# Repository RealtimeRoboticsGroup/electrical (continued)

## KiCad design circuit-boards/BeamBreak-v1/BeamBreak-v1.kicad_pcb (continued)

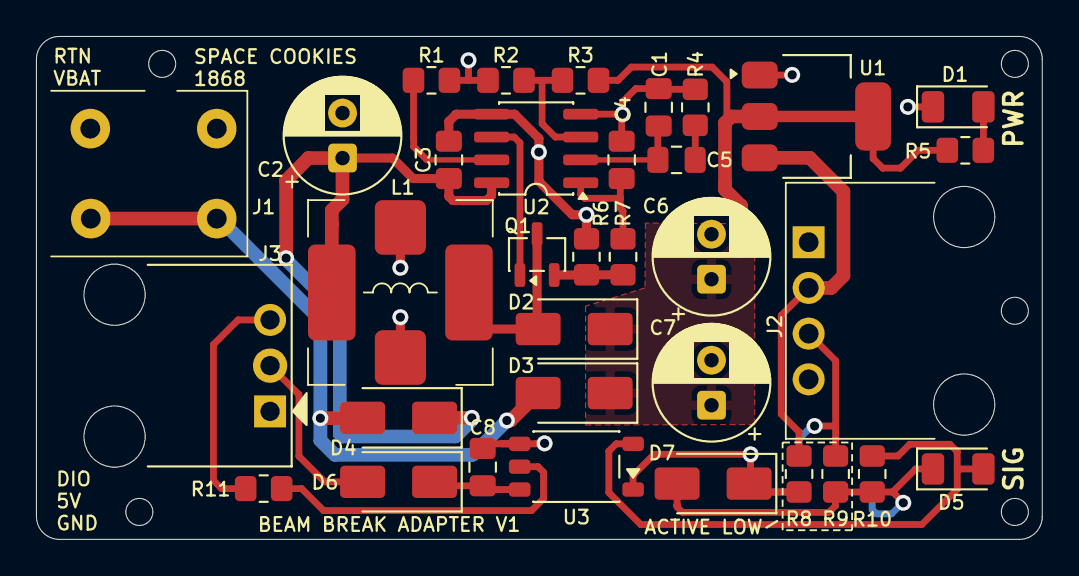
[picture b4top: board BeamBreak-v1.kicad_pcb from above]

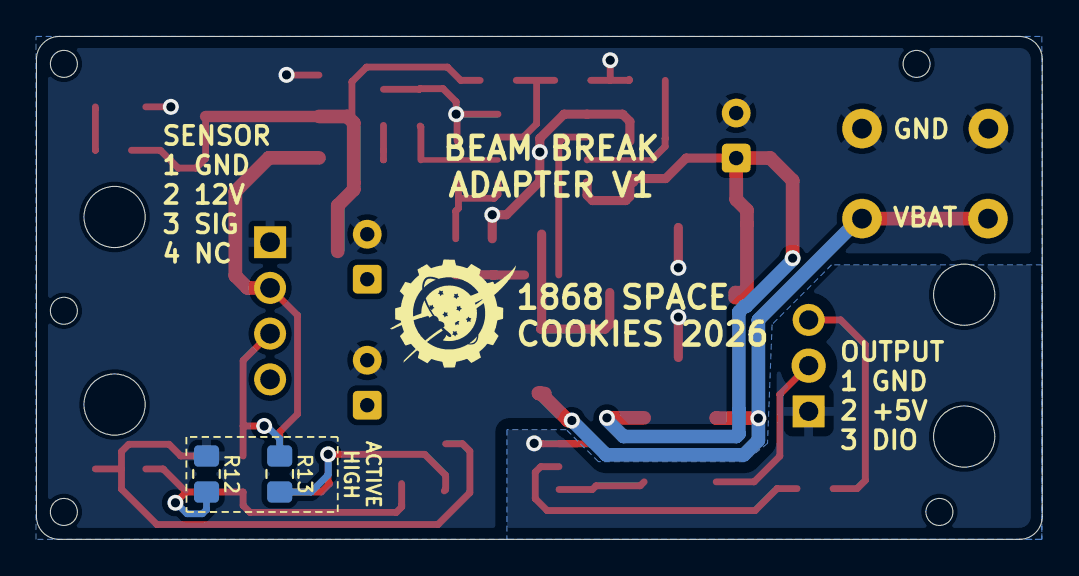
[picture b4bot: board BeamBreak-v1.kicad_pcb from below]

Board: 2 copper layers, 55.9 x 27.9 mm, 41 parts (3 on the bottom side), 23 nets.

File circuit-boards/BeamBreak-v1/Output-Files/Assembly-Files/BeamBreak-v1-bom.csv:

"Item","QUANTITY","Reference","Value","MFG","MFG P/N","DIST","DIST P/N"
"1","1","C1","1nF-50V-5%-0805","KEMET","C0805C102J5GACTU","Digikey","399-C0805C102J5GACTUCT-ND"
"2","1","C4","10pF-50V-5%-0805","YAGEO","CC0805JRNPO9BN100","Digikey","311-1099-1-ND"
"3","1","C5","22nF-50V-5%-0805","TDK Corporation","C2012C0G1H223J125AA","Digikey","445-7522-1-ND"
"4","3","C2,C6,C7","100uF-20%-35V","KYOCERA AVX","RPF0608101M035K","Digikey","478-RPF0608101M035KCT-ND"
"5","2","C3,C8","0.1uF-50V-5%-0805","KEMET","C0805C104J5RACTU","Digikey","399-C0805C104J5RACTUCT-ND"
"6","1","D1","PWR","Everlight","QTLP650D4TR/QT15-21SYGD/S530-E2/TR8","Digikey","1080-1419-1-ND"
"7","1","D5","SIG","Everlight","QTLP650D3TR","Digikey","1080-1418-1-ND"
"8","5","D2-D4,D6,D7","B340AE-13","Diodes Inc","B340AE-13","Digikey","B340AE-13DICT-ND"
"9","1","J1","Power","Weidmuller","1824740000","Digikey","281-2110-ND"
"10","1","J2","SENSOR","Molex","70555-0038","Digikey","WM4177-ND"
"11","1","J3","OUT","Molex","70555-0037","Digikey","WM4176-ND"
"12","1","L1","33uH-159m-20%","Vishay Dale","IHLE5050FHER6R8M5A","Digikey","541-IHLE5050FHER6R8M5ACT-ND"
"13","1","Q1","SI2318CDS-T1-GE3","Vishay Siliconix","SI2318CDS-T1-GE3","Digikey","SI2318CDS-T1-GE3CT-ND"
"14","1","R1","59.0k-1%-0805","YAGEO","RC0805FR-0759KL","Digikey","311-59.0KCRCT-ND"
"15","1","R2","1k-1%-0805","YAGEO","RC0805FR-071KL","Digikey","311-1.00KCRCT-ND"
"16","1","R3","8.66k-1%-0805","Stackpole Electronics Inc","RMCF0805FT8K66","Digikey","RMCF0805FT8K66CT-ND"
"17","1","R4","7.32k-1%-0805","Panasonic Electronic Components","ERJ-6ENF7321V","Digikey","P7.32KCCT-ND"
"18","1","R5","2k-1%-0805","Vishay Dale","CRCW08052K00FKEA","Digikey","541-2.00KCCT-ND"
"19","1","R6","50mOhm-1%-0805","Panasonic Electronic Components","ERJ-6BWFR050V","Digikey","P17581CT-ND"
"20","2","R7,R11","100R-1%-0805","TE Connectivity Passive Product","CRG0805F100R","Digikey","A106053CT-ND"
"21","3","R8-R10","499R-1%-0805","YAGEO","RC0805FR-07499RL","Digikey","311-499CRCT-ND"
"22","1","U1","ITS41k0S-ME-N","Infineon","ITS41K0SMENHUMA1","Digikey","ITS41K0SMENHUMA1CT-ND"
"23","1","U2","LM3478MA","Texas Instruments","LM3478MAX/NOPB","Digikey","296-38111-1-ND"
"24","1","U3","TLP2361(TPL,E","Toshiba Semiconductor and Storage","TLP2361(TPL,E","Digikey","TLP2361(TPLECT-ND"

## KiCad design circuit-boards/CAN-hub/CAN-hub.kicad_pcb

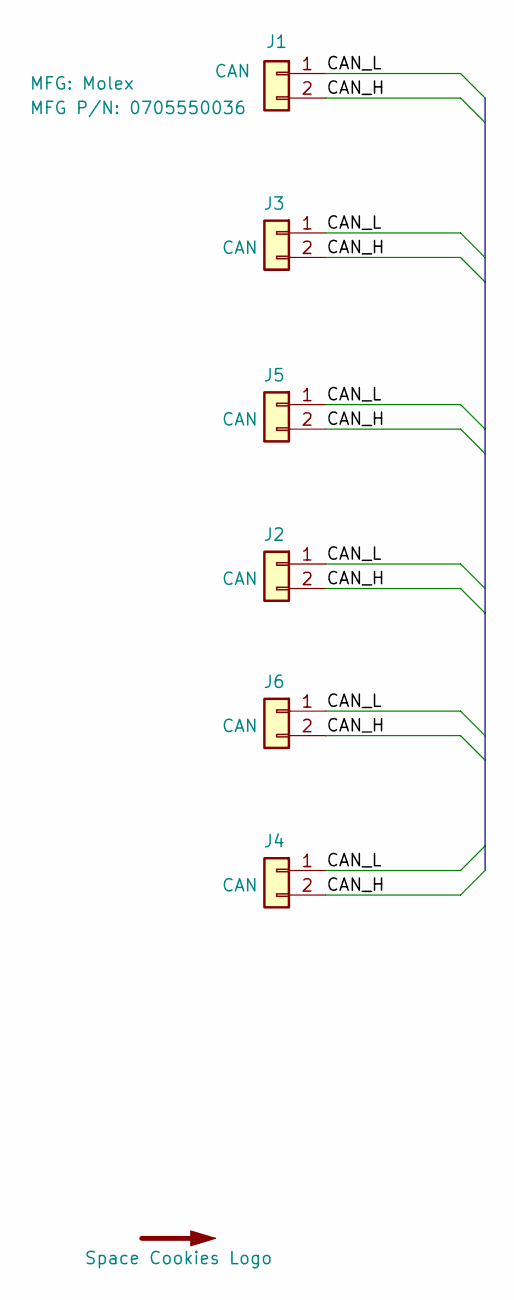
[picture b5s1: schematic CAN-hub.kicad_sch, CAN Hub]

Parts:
G1: Space Cookies Logo; SPACE_COOKIES_LOGO_7mm
J1, J2, J3, J4, J5, J6: CAN; Molex-70555-0001; MFG P/N 0705550036

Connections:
/CAN_H: J1.2, J2.2, J3.2, J4.2, J5.2, J6.2
/CAN_L: J1.1, J2.1, J3.1, J4.1, J5.1, J6.1

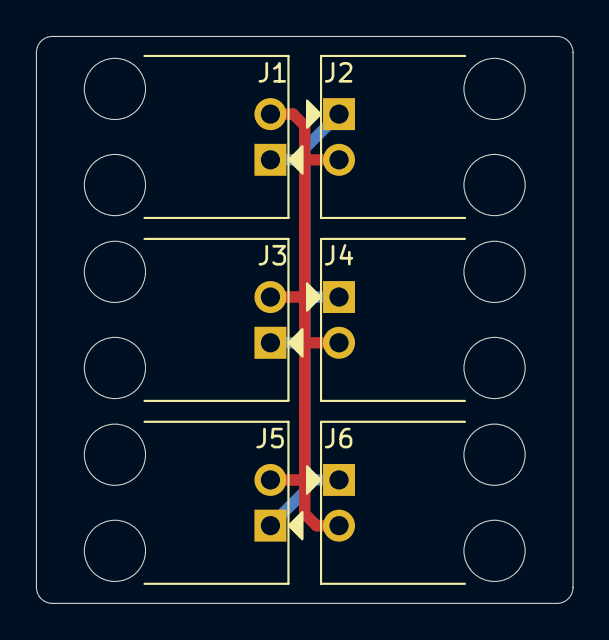
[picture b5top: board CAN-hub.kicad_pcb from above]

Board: 2 copper layers, 29.8 x 31.5 mm, 7 parts (1 on the bottom side), 2 nets.

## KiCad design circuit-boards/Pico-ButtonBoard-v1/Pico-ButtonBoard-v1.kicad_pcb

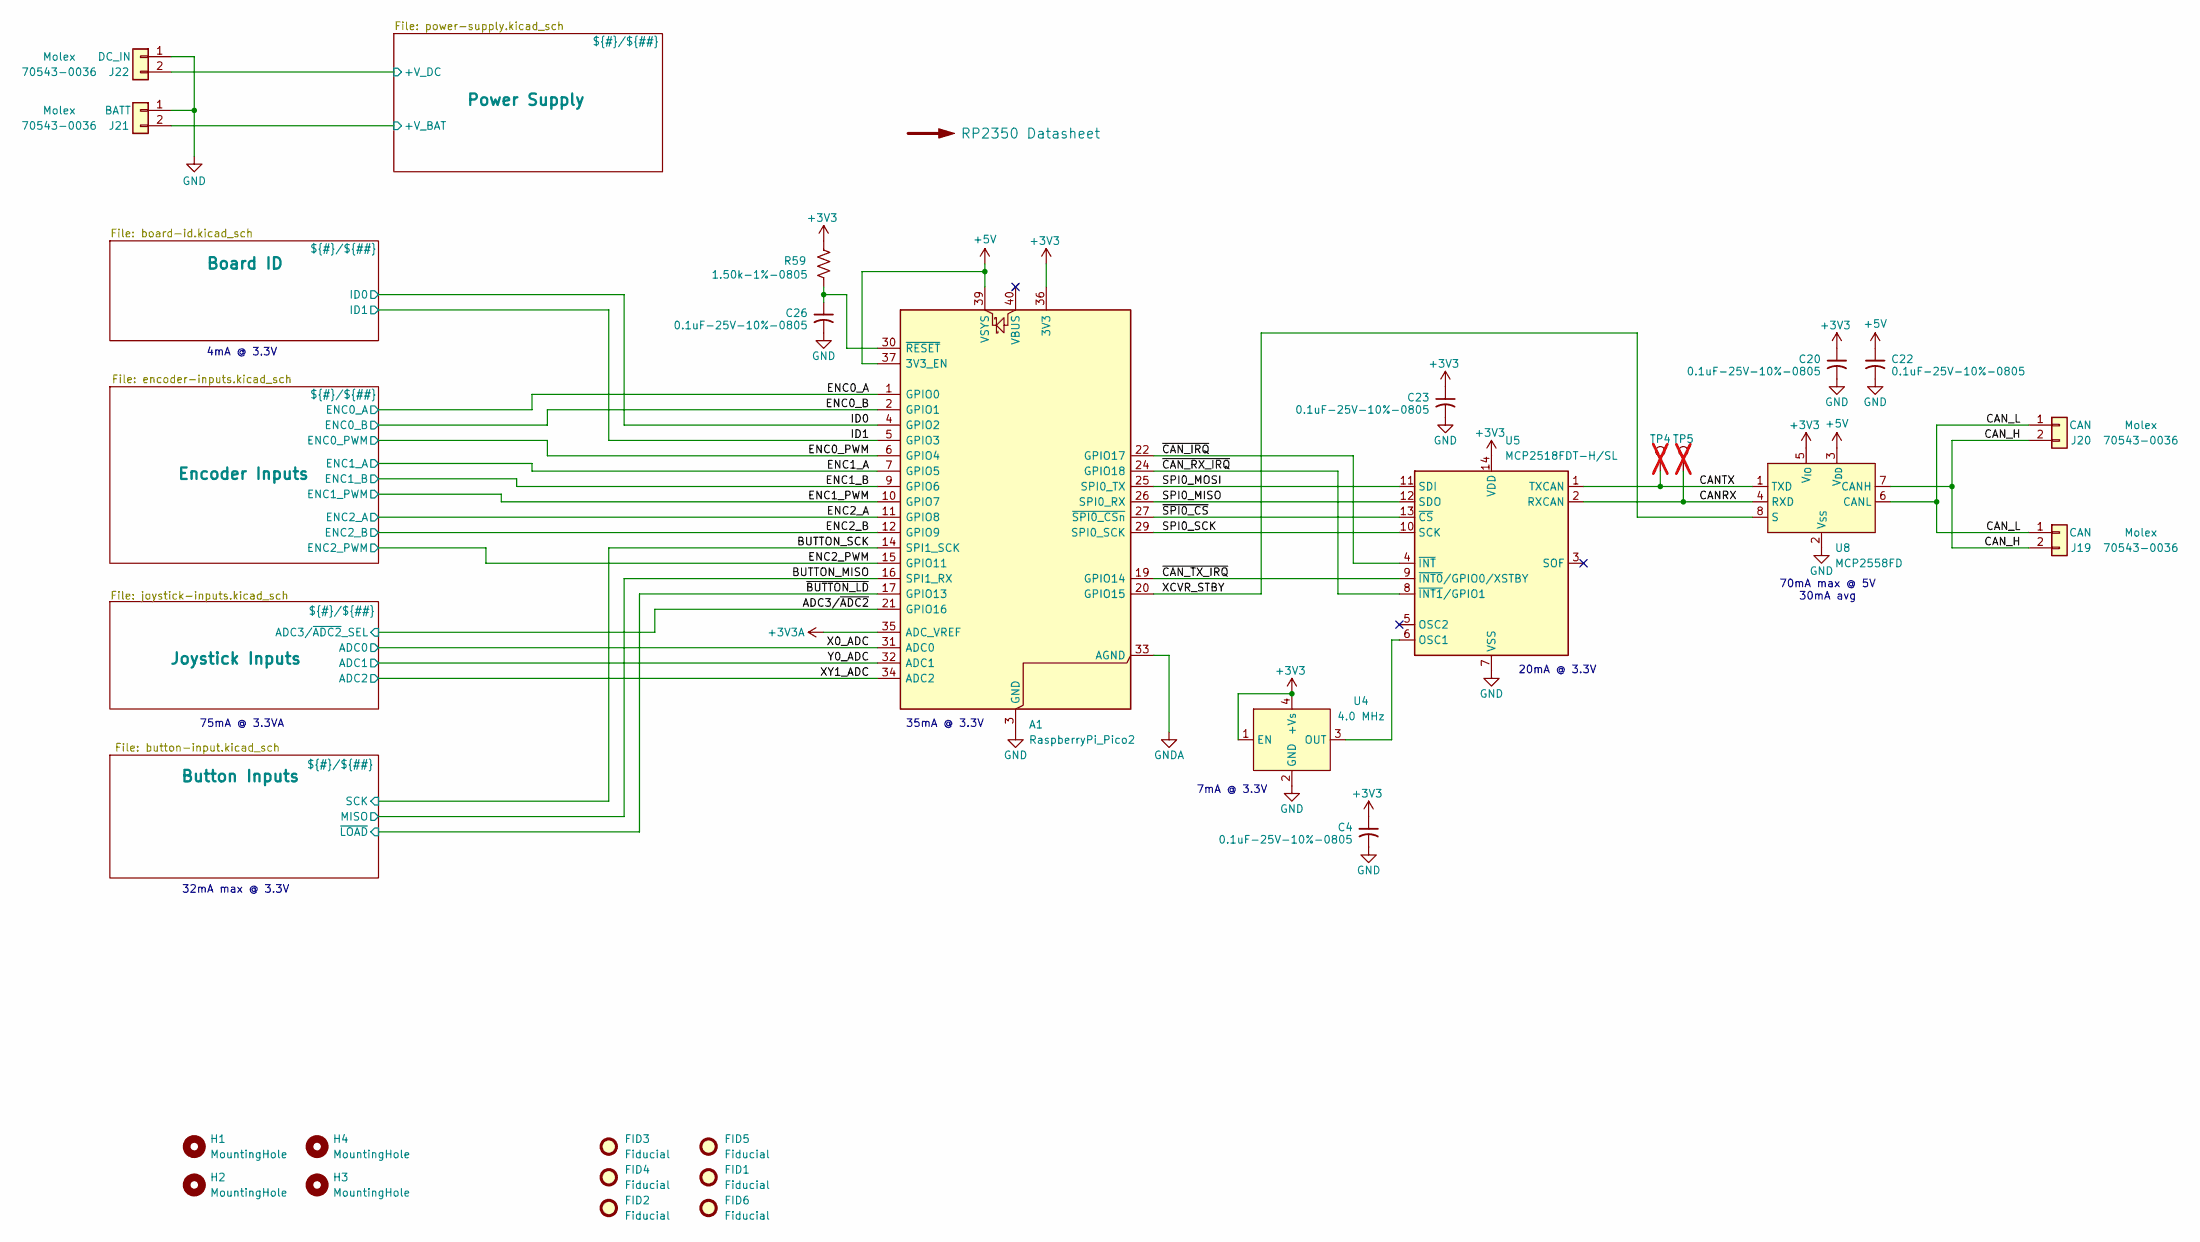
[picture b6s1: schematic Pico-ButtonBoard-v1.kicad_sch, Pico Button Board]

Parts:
A1: RaspberryPi_Pico2; RaspberryPi_Pico_Common_Unspecified
C4, C20, C22, C23, C26: 0.1uF-25V-10%-0805; C_0805_2012Metric_Pad1.18x1.45mm_HandSolder; MFG P/N 311-1141-1-ND
FID1, FID2, FID3, FID4, FID5, FID6: Fiducial; Fiducial_1.6mm_Mask3mm
H1, H2, H3, H4: MountingHole; MountingHole_3.2mm_M3
J19, J20: CAN; Molex-70543-0001; MFG P/N 70543-0036
J21: BATT; Molex-70543-0001; MFG P/N 70543-0036
J22: DC_IN; Molex-70543-0001; MFG P/N 70543-0036
R59: 1.50k-1%-0805; R_0805_2012Metric_Pad1.20x1.40mm_HandSolder; MFG P/N RC0805FR-071K5L
TP4: CAN_TX; TestPoint_Keystone_5000-5004_Miniature; not fitted
TP5: CAN_RX; TestPoint_Keystone_5000-5004_Miniature; not fitted
U4: 4.0 MHz; Wurth-CFPS-73; MFG P/N 831018041
U5: MCP2518FDT-H/SL; SO-14_3.9x8.65mm_P1.27mm; MFG P/N MCP2518FDT-H/SL
U8: MCP2558FD; SO-8_3.9x4.9mm_P1.27mm; MFG P/N MCP2558FD-H/SN

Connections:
+3V3: A1.36 (3V3), C4.1, C20.1, C23.1, R59.1, U4.1 (EN), U4.4 (+Vs), U5.14 (VDD), U8.5 (V_{IO}); also elsewhere on the board
+3V3A: A1.35 (ADC_VREF); also elsewhere on the board
+5V: A1.37 (3V3_EN), A1.39 (VSYS), C22.1, U8.3 (V_{DD}); also elsewhere on the board
/ADC3/~ADC2: A1.21 (GPIO16); also elsewhere on the board
/BUTTON_MISO: A1.16 (SPI1_RX); also elsewhere on the board
/BUTTON_SCK: A1.14 (SPI1_SCK); also elsewhere on the board
/CANRX: TP5.1, U5.2 (RXCAN), U8.4 (RXD)
/CANTX: TP4.1, U5.1 (TXCAN), U8.1 (TXD)
/CAN_H: J19.2, J20.2, U8.7 (CANH)
/CAN_L: J19.1, J20.1, U8.6 (CANL)
/ENC0_A: A1.1 (GPIO0); also elsewhere on the board
/ENC0_B: A1.2 (GPIO1); also elsewhere on the board
/ENC0_PWM: A1.6 (GPIO4); also elsewhere on the board
/ENC1_A: A1.7 (GPIO5); also elsewhere on the board
/ENC1_B: A1.9 (GPIO6); also elsewhere on the board
/ENC1_PWM: A1.10 (GPIO7); also elsewhere on the board
/ENC2_A: A1.11 (GPIO8); also elsewhere on the board
/ENC2_B: A1.12 (GPIO9); also elsewhere on the board
/ENC2_PWM: A1.15 (GPIO11); also elsewhere on the board
/ID0: A1.4 (GPIO2); also elsewhere on the board
/ID1: A1.5 (GPIO3); also elsewhere on the board
/Power Supply/+V_BAT: J21.2; also elsewhere on the board
/Power Supply/+V_DC: J22.2; also elsewhere on the board
/SPI0_MISO: A1.26 (SPI0_RX), U5.12 (SDO)
/SPI0_MOSI: A1.25 (SPI0_TX), U5.11 (SDI)
/SPI0_SCK: A1.29 (SPI0_SCK), U5.10 (SCK)
/X0_ADC: A1.31 (ADC0); also elsewhere on the board
/XCVR_STBY: A1.20 (GPIO15), U8.8 (S)
/XY1_ADC: A1.34 (ADC2); also elsewhere on the board
/Y0_ADC: A1.32 (ADC1); also elsewhere on the board
/~BUTTON_LD: A1.17 (GPIO13); also elsewhere on the board
/~CAN_IRQ: A1.22 (GPIO17), U5.4 (~INT)
/~CAN_RX_IRQ: A1.24 (GPIO18), U5.8 (~INT1/GPIO1)
/~CAN_TX_IRQ: A1.19 (GPIO14), U5.9 (~INT0/GPIO0/XSTBY)
/~SPI0_CS: A1.27 (~SPI0_CSn), U5.13 (~CS)
GND: A1.3 (GND), A1.8 (GND), A1.13 (GND), A1.18 (GND), A1.23 (GND), A1.28 (GND), A1.38 (GND), C4.2, C20.2, C22.2, C23.2, C26.2, J21.1, J22.1, U4.2 (GND), U5.7 (VSS), U8.2 (V_{SS}); also elsewhere on the board
GNDA: A1.33 (AGND); also elsewhere on the board
unnamed: A1.30 (~RESET), C26.1, R59.2
unnamed: U4.3 (OUT), U5.6 (OSC1)

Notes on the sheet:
32mA max @ 3.3V
20mA @ 3.3V
35mA @ 3.3V
75mA @ 3.3VA
4mA @ 3.3V
7mA @ 3.3V
70mA max @ 5V 30mA avg

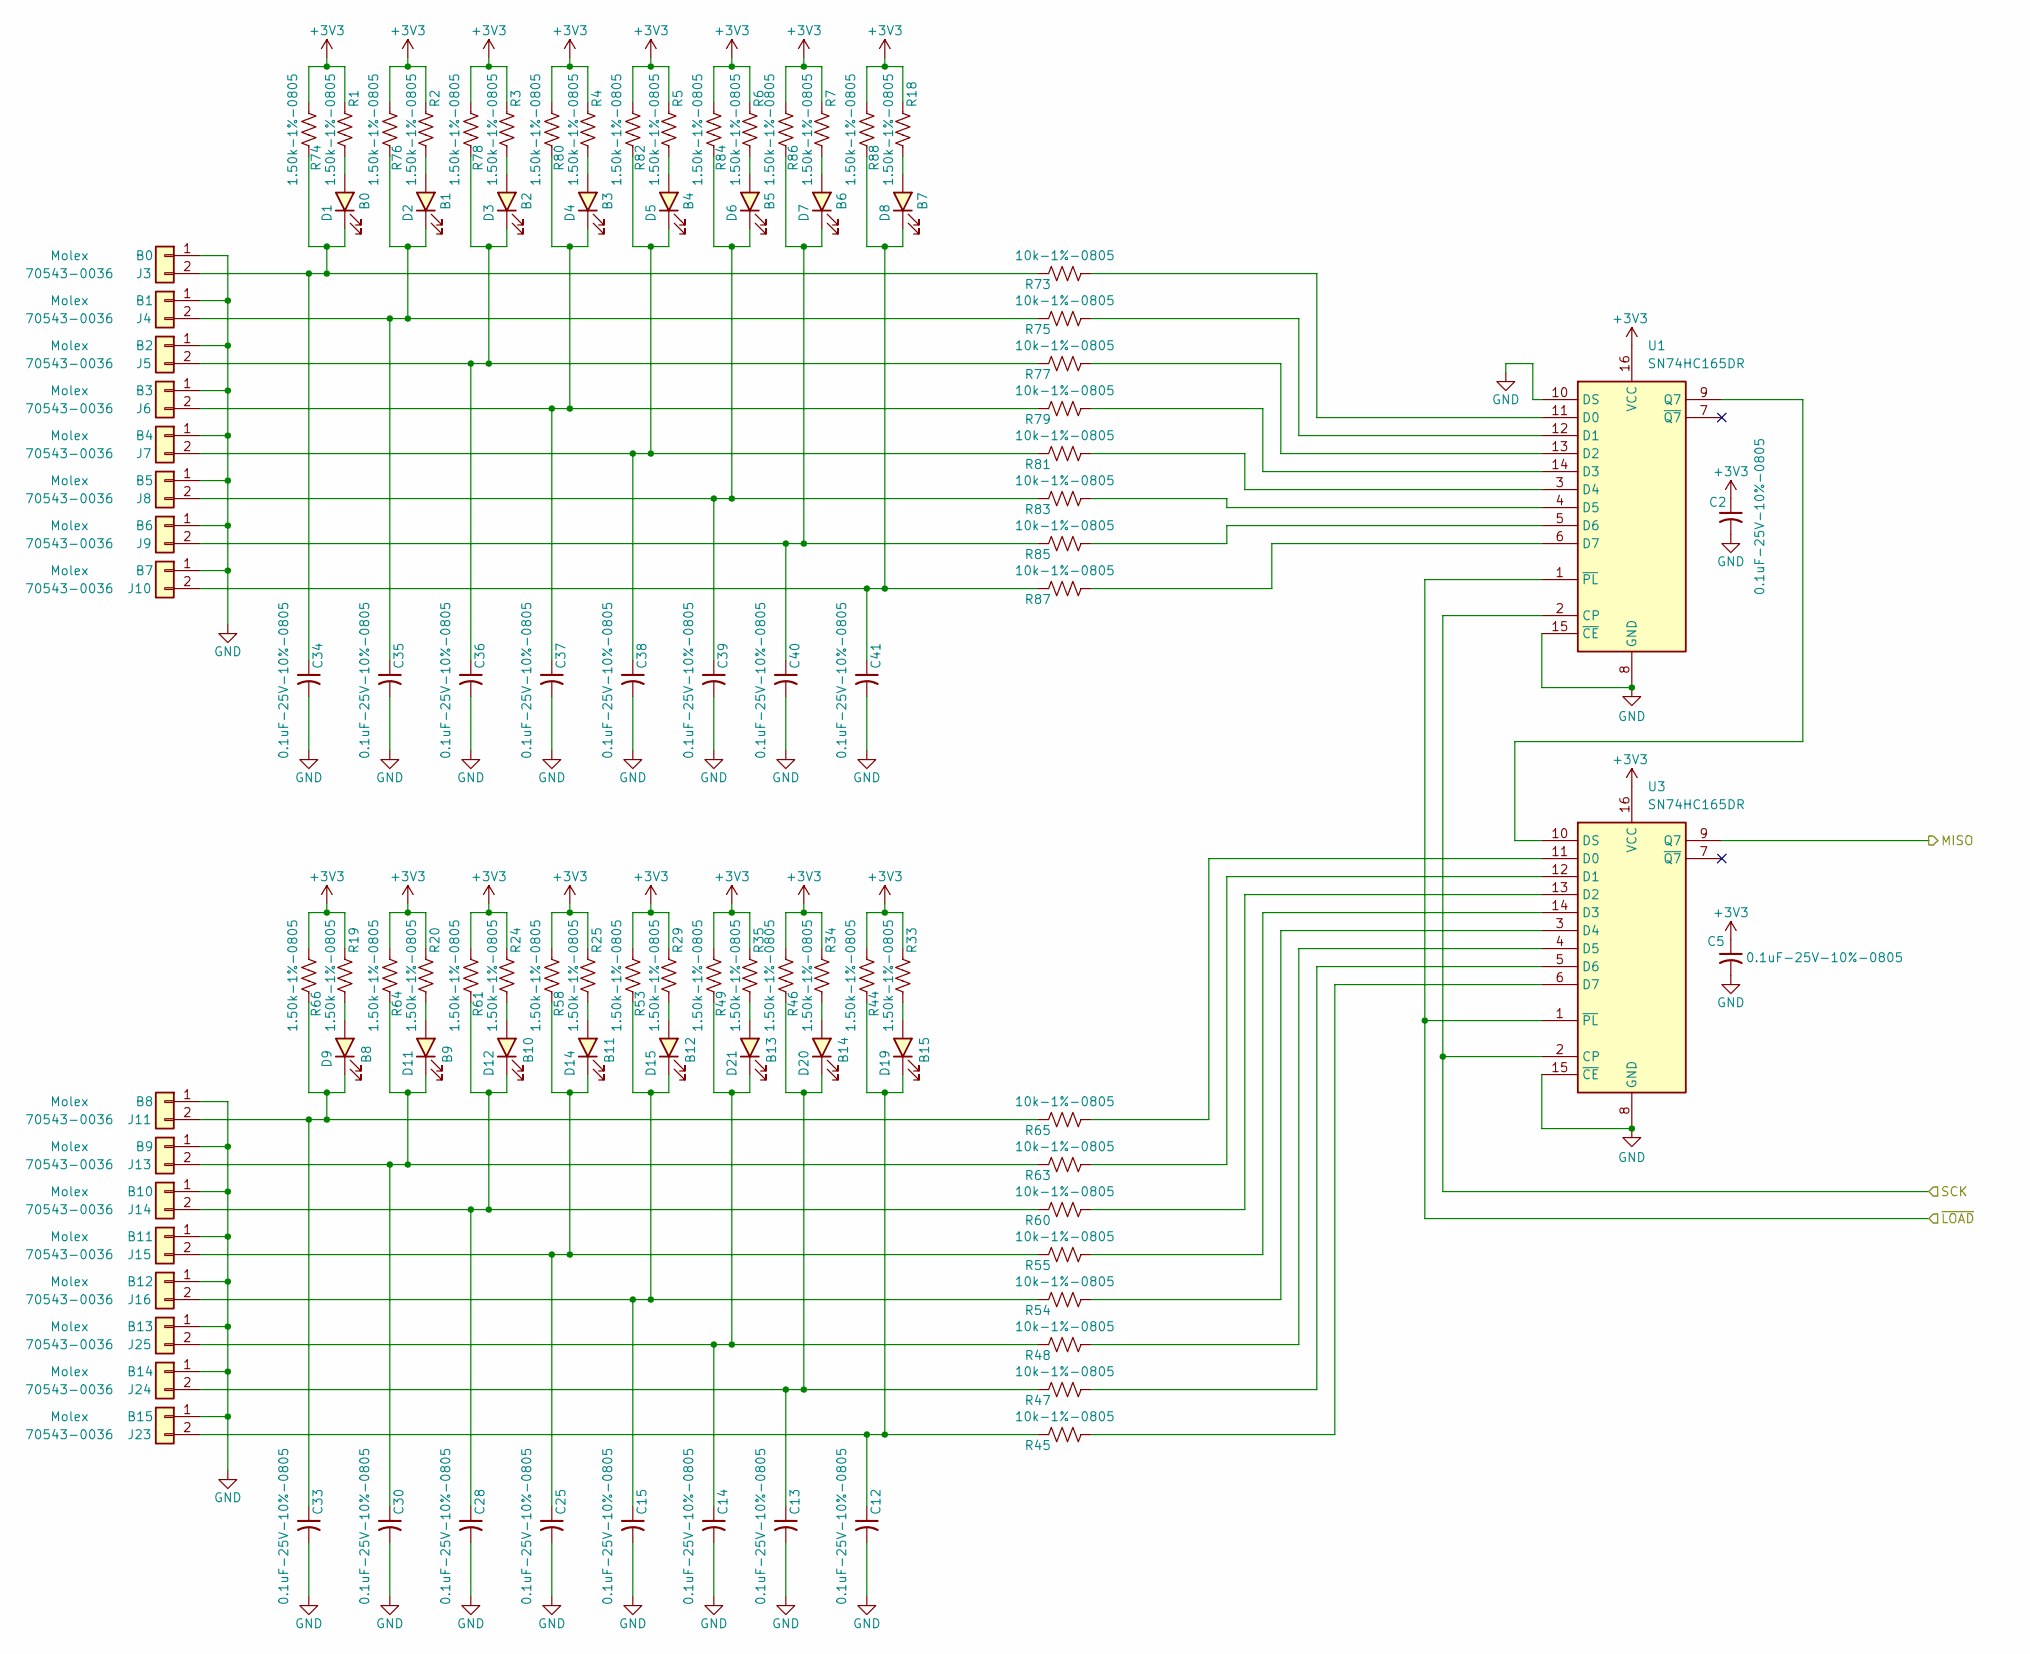
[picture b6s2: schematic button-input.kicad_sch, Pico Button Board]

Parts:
C2, C5, C12, C13, C14, C15, C25, C28, C30, C33, C34, C35, C36, C37, C38, C39, C40, C41: 0.1uF-25V-10%-0805; C_0805_2012Metric_Pad1.18x1.45mm_HandSolder; MFG P/N 311-1141-1-ND
D1: B0; LED_1206_3216Metric; MFG P/N QTLP650D4TR/QT15-21SYGD/S530-E2/TR8
D2: B1; LED_1206_3216Metric; MFG P/N QTLP650D4TR/QT15-21SYGD/S530-E2/TR8
D3: B2; LED_1206_3216Metric; MFG P/N QTLP650D4TR/QT15-21SYGD/S530-E2/TR8
D4: B3; LED_1206_3216Metric; MFG P/N QTLP650D4TR/QT15-21SYGD/S530-E2/TR8
D5: B4; LED_1206_3216Metric; MFG P/N QTLP650D4TR/QT15-21SYGD/S530-E2/TR8
D6: B5; LED_1206_3216Metric; MFG P/N QTLP650D4TR/QT15-21SYGD/S530-E2/TR8
D7: B6; LED_1206_3216Metric; MFG P/N QTLP650D4TR/QT15-21SYGD/S530-E2/TR8
D8: B7; LED_1206_3216Metric; MFG P/N QTLP650D4TR/QT15-21SYGD/S530-E2/TR8
D9: B8; LED_1206_3216Metric; MFG P/N QTLP650D4TR/QT15-21SYGD/S530-E2/TR8
D11: B9; LED_1206_3216Metric; MFG P/N QTLP650D4TR/QT15-21SYGD/S530-E2/TR8
D12: B10; LED_1206_3216Metric; MFG P/N QTLP650D4TR/QT15-21SYGD/S530-E2/TR8
D14: B11; LED_1206_3216Metric; MFG P/N QTLP650D4TR/QT15-21SYGD/S530-E2/TR8
D15: B12; LED_1206_3216Metric; MFG P/N QTLP650D4TR/QT15-21SYGD/S530-E2/TR8
D19: B15; LED_1206_3216Metric; MFG P/N QTLP650D4TR/QT15-21SYGD/S530-E2/TR8
D20: B14; LED_1206_3216Metric; MFG P/N QTLP650D4TR/QT15-21SYGD/S530-E2/TR8
D21: B13; LED_1206_3216Metric; MFG P/N QTLP650D4TR/QT15-21SYGD/S530-E2/TR8
J3: B0; Molex-70543-0001; MFG P/N 70543-0036
J4: B1; Molex-70543-0001; MFG P/N 70543-0036
J5: B2; Molex-70543-0001; MFG P/N 70543-0036
J6: B3; Molex-70543-0001; MFG P/N 70543-0036
J7: B4; Molex-70543-0001; MFG P/N 70543-0036
J8: B5; Molex-70543-0001; MFG P/N 70543-0036
J9: B6; Molex-70543-0001; MFG P/N 70543-0036
J10: B7; Molex-70543-0001; MFG P/N 70543-0036
J11: B8; Molex-70543-0001; MFG P/N 70543-0036
J13: B9; Molex-70543-0001; MFG P/N 70543-0036
J14: B10; Molex-70543-0001; MFG P/N 70543-0036
J15: B11; Molex-70543-0001; MFG P/N 70543-0036
J16: B12; Molex-70543-0001; MFG P/N 70543-0036
J23: B15; Molex-70543-0001; MFG P/N 70543-0036
J24: B14; Molex-70543-0001; MFG P/N 70543-0036
J25: B13; Molex-70543-0001; MFG P/N 70543-0036
R1, R2, R3, R4, R5, R6, R7, R18, R19, R20, R24, R25, R29, R33, R34, R35, R44, R46, R49, R53, R58, R61, R64, R66, R74, R76, R78, R80, R82, R84, R86, R88: 1.50k-1%-0805; R_0805_2012Metric_Pad1.20x1.40mm_HandSolder; MFG P/N RC0805FR-071K5L
R45, R47, R48, R54, R55, R60, R63, R65, R73, R75, R77, R79, R81, R83, R85, R87: 10k-1%-0805; R_0805_2012Metric_Pad1.20x1.40mm_HandSolder; MFG P/N CRCW080510K0FKEA
U1, U3: SN74HC165DR; SO-16_3.9x9.9mm_P1.27mm; MFG P/N SN74HC165DR

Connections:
+3V3: C2.1, C5.1, R1.1, R2.1, R3.1, R4.1, R5.1, R6.1, R7.1, R18.1, R19.1, R20.1, R24.1, R25.1, R29.1, R33.1, R34.1, R35.1, R44.1, R46.1, R49.1, R53.1, R58.1, R61.1, R64.1, R66.1, R74.1, R76.1, R78.1, R80.1, R82.1, R84.1, R86.1, R88.1, U1.16 (VCC), U3.16 (VCC); also elsewhere on the board
/BUTTON_MISO: U3.9 (Q7); also elsewhere on the board
/BUTTON_SCK: U1.2 (CP), U3.2 (CP); also elsewhere on the board
/~BUTTON_LD: U1.1 (~PL), U3.1 (~PL); also elsewhere on the board
GND: C2.2, C5.2, C12.2, C13.2, C14.2, C15.2, C25.2, C28.2, C30.2, C33.2, C34.2, C35.2, C36.2, C37.2, C38.2, C39.2, C40.2, C41.2, J3.1, J4.1, J5.1, J6.1, J7.1, J8.1, J9.1, J10.1, J11.1, J13.1, J14.1, J15.1, J16.1, J23.1, J24.1, J25.1, U1.8 (GND), U1.10 (DS), U1.15 (~CE), U3.8 (GND), U3.15 (~CE); also elsewhere on the board
unnamed: D1.2 (A), R1.2
unnamed: C34.1, D1.1 (K), J3.2, R73.1, R74.2
unnamed: D2.2 (A), R2.2
unnamed: C35.1, D2.1 (K), J4.2, R75.1, R76.2
unnamed: D3.2 (A), R3.2
unnamed: C36.1, D3.1 (K), J5.2, R77.1, R78.2
unnamed: D4.2 (A), R4.2
unnamed: C37.1, D4.1 (K), J6.2, R79.1, R80.2
unnamed: D5.2 (A), R5.2
unnamed: C38.1, D5.1 (K), J7.2, R81.1, R82.2
unnamed: D6.2 (A), R6.2
unnamed: C39.1, D6.1 (K), J8.2, R83.1, R84.2
unnamed: D7.2 (A), R7.2
unnamed: C40.1, D7.1 (K), J9.2, R85.1, R86.2
unnamed: D8.2 (A), R18.2
unnamed: C41.1, D8.1 (K), J10.2, R87.1, R88.2
unnamed: D9.2 (A), R19.2
unnamed: C33.1, D9.1 (K), J11.2, R65.1, R66.2
unnamed: D11.2 (A), R20.2
unnamed: C30.1, D11.1 (K), J13.2, R63.1, R64.2
unnamed: D12.2 (A), R24.2
unnamed: C28.1, D12.1 (K), J14.2, R60.1, R61.2
unnamed: D14.2 (A), R25.2
unnamed: C25.1, D14.1 (K), J15.2, R55.1, R58.2
unnamed: D15.2 (A), R29.2
unnamed: C15.1, D15.1 (K), J16.2, R53.2, R54.1
unnamed: D19.2 (A), R33.2
unnamed: C12.1, D19.1 (K), J23.2, R44.2, R45.1
unnamed: D20.2 (A), R34.2
unnamed: C13.1, D20.1 (K), J24.2, R46.2, R47.1
unnamed: D21.2 (A), R35.2
unnamed: C14.1, D21.1 (K), J25.2, R48.1, R49.2
unnamed: R73.2, U1.11 (D0)
unnamed: R75.2, U1.12 (D1)
unnamed: R77.2, U1.13 (D2)
unnamed: R79.2, U1.14 (D3)
unnamed: R81.2, U1.3 (D4)
unnamed: R83.2, U1.4 (D5)
unnamed: R85.2, U1.5 (D6)
unnamed: R87.2, U1.6 (D7)
unnamed: U1.9 (Q7), U3.10 (DS)
unnamed: R65.2, U3.11 (D0)
unnamed: R63.2, U3.12 (D1)
unnamed: R60.2, U3.13 (D2)
unnamed: R55.2, U3.14 (D3)
unnamed: R54.2, U3.3 (D4)
unnamed: R48.2, U3.4 (D5)
unnamed: R47.2, U3.5 (D6)
unnamed: R45.2, U3.6 (D7)

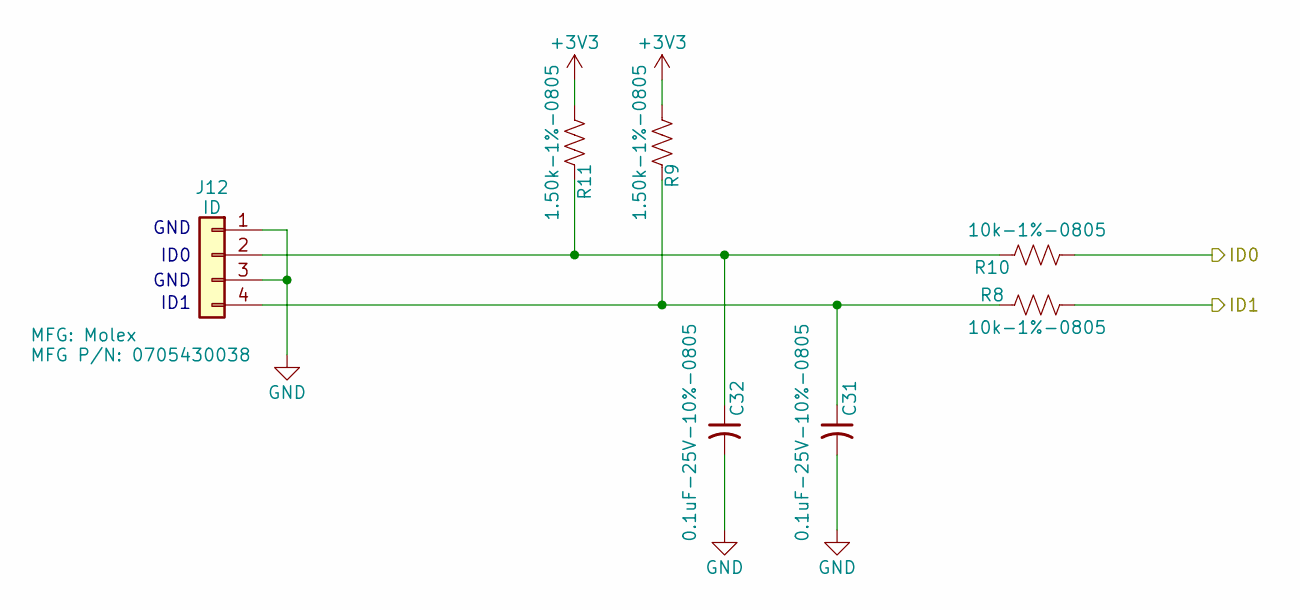
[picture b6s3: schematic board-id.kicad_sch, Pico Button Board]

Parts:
C31, C32: 0.1uF-25V-10%-0805; C_0805_2012Metric_Pad1.18x1.45mm_HandSolder; MFG P/N 311-1141-1-ND
J12: ID; Molex-70543-0003; MFG P/N 0705430038
R8, R10: 10k-1%-0805; R_0805_2012Metric_Pad1.20x1.40mm_HandSolder; MFG P/N CRCW080510K0FKEA
R9, R11: 1.50k-1%-0805; R_0805_2012Metric_Pad1.20x1.40mm_HandSolder; MFG P/N RC0805FR-071K5L

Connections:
+3V3: R9.1, R11.1; also elsewhere on the board
/ID0: R10.2; also elsewhere on the board
/ID1: R8.2; also elsewhere on the board
GND: C31.2, C32.2, J12.1, J12.3; also elsewhere on the board
unnamed: C32.1, J12.2, R10.1, R11.2
unnamed: C31.1, J12.4, R8.1, R9.2

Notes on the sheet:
GND
ID1
ID0

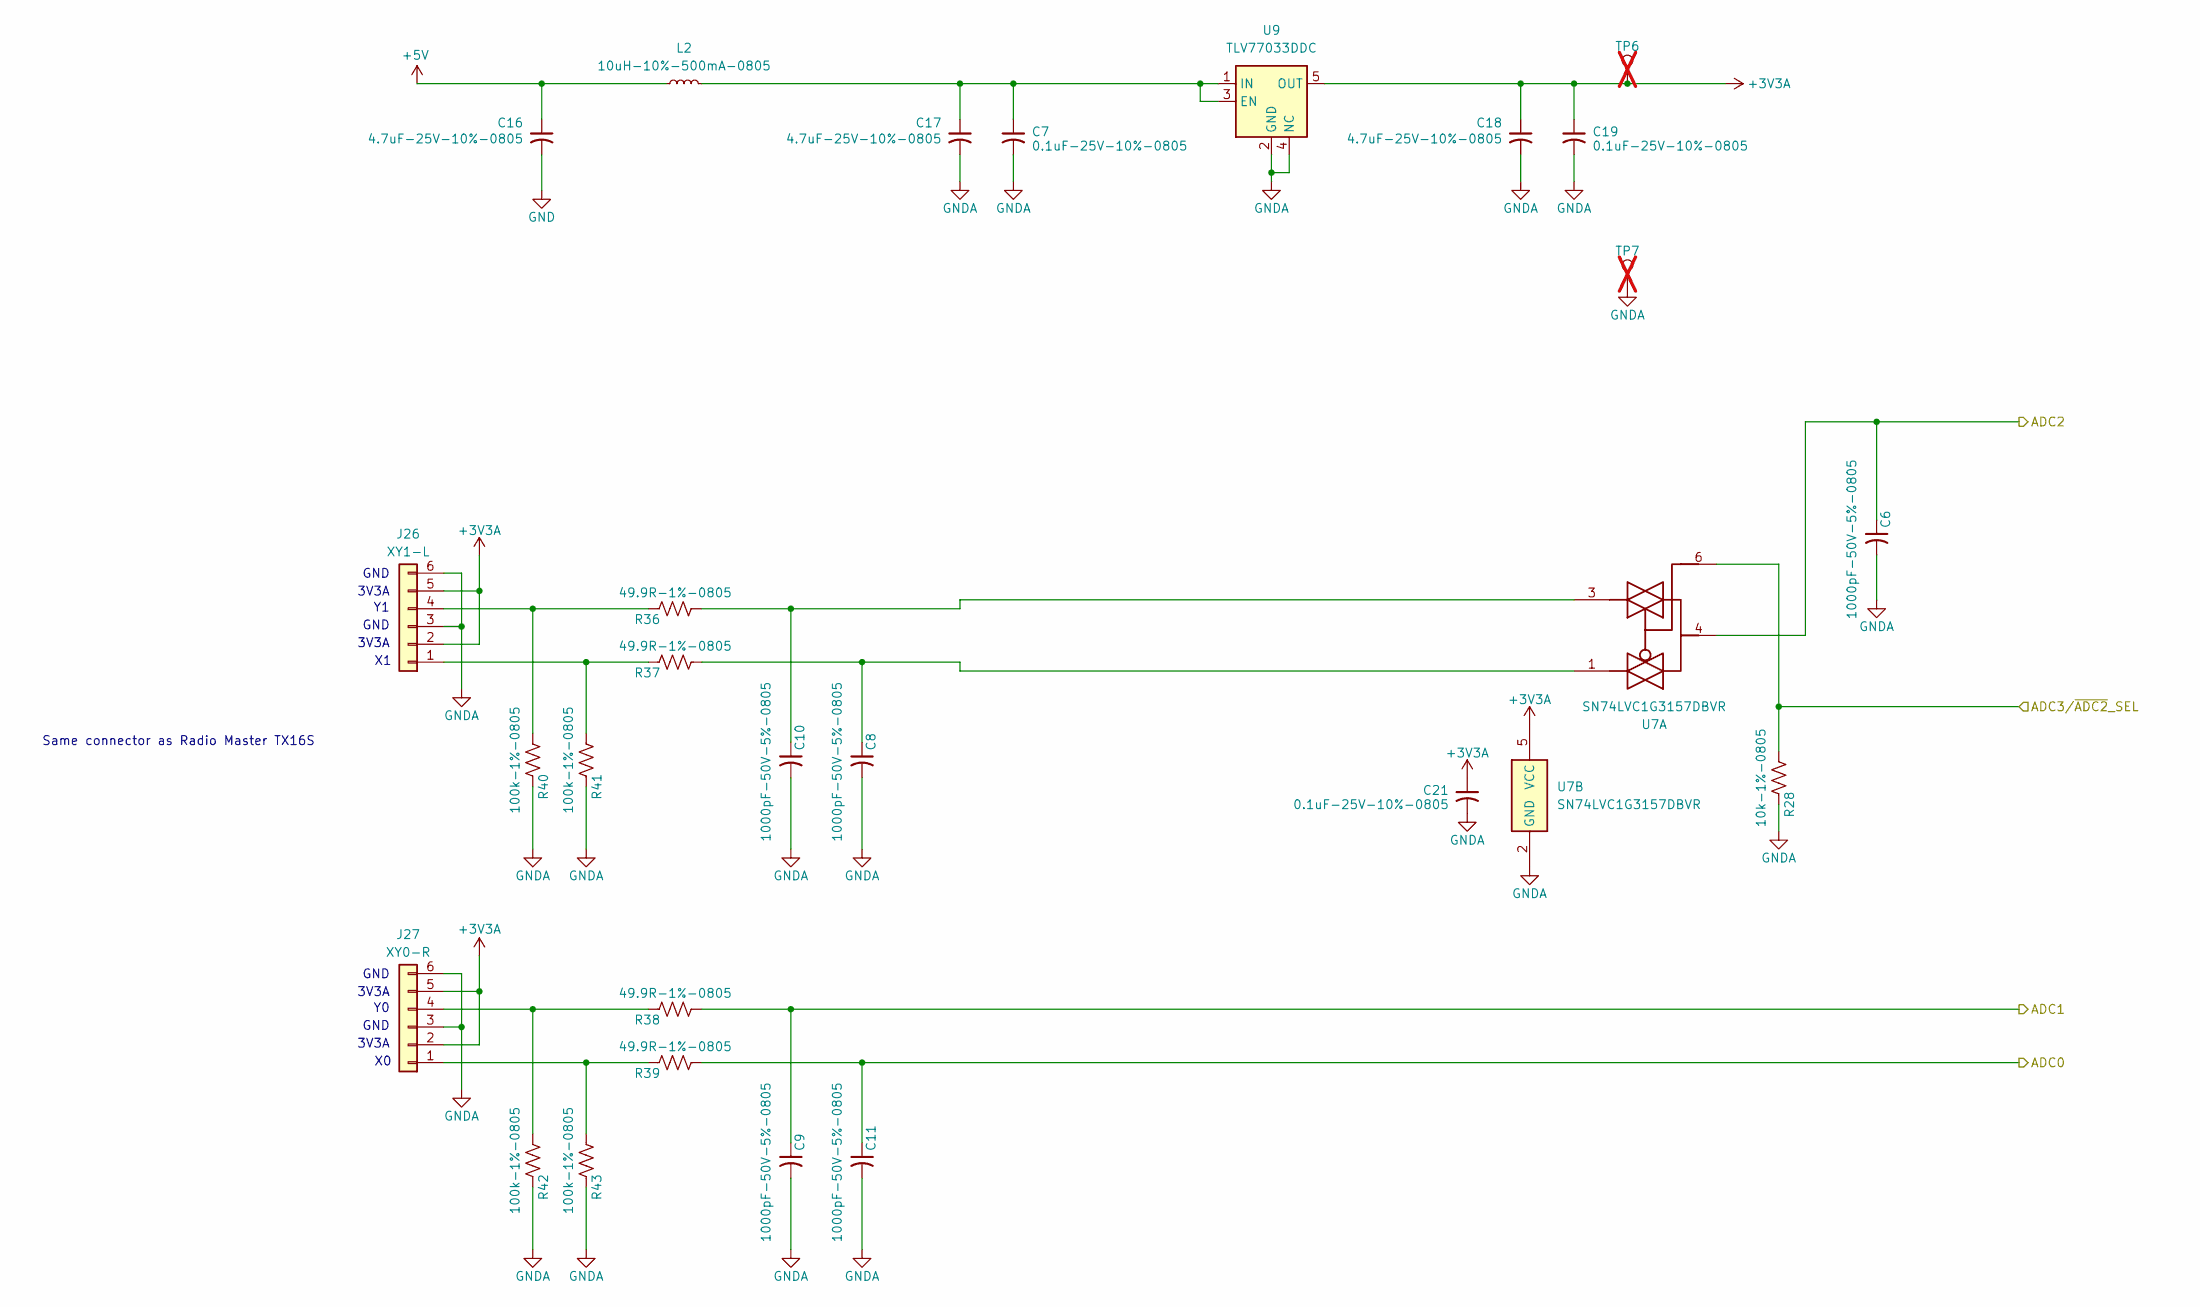
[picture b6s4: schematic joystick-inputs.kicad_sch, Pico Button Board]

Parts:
C6, C8, C9, C10, C11: 1000pF-50V-5%-0805; C_0805_2012Metric_Pad1.18x1.45mm_HandSolder; MFG P/N C0805C102J5GACTU
C7, C19, C21: 0.1uF-25V-10%-0805; C_0805_2012Metric_Pad1.18x1.45mm_HandSolder; MFG P/N 311-1141-1-ND
C16, C17, C18: 4.7uF-25V-10%-0805; C_0805_2012Metric_Pad1.18x1.45mm_HandSolder; MFG P/N C2012X5R1E475K125AB
J26: XY1-L; Molex_PicoBlade_53047-0610_1x06_P1.25mm_Vertical; MFG P/N 530470610
J27: XY0-R; Molex_PicoBlade_53047-0610_1x06_P1.25mm_Vertical; MFG P/N 530470610
L2: 10uH-10%-500mA-0805; L_0805_2012Metric_Pad1.05x1.20mm_HandSolder; MFG P/N MLZ2012N100LT000
R28: 10k-1%-0805; R_0805_2012Metric_Pad1.20x1.40mm_HandSolder; MFG P/N CRCW080510K0FKEA
R36, R37, R38, R39: 49.9R-1%-0805; R_0805_2012Metric_Pad1.20x1.40mm_HandSolder; MFG P/N RMCF0805FT49R9
R40, R41, R42, R43: 100k-1%-0805; R_0805_2012Metric_Pad1.20x1.40mm_HandSolder; MFG P/N RC0805FR-07100KL
TP6, TP7: CAN_RX; TestPoint_Keystone_5000-5004_Miniature; not fitted
U7: SN74LVC1G3157DBVR; SOT-23-6_Handsoldering; MFG P/N SN74LVC1G3157DBVR
U9: TLV77033DDC; SOT-23-5; MFG P/N TLV70033DDCR

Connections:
+3V3A: C18.1, C19.1, C21.1, J26.2, J26.5, J27.2, J27.5, TP6.1, U7.5 (VCC), U9.5 (OUT); also elsewhere on the board
+5V: C16.1, L2.1; also elsewhere on the board
/ADC3/~ADC2: R28.2, U7.6; also elsewhere on the board
/X0_ADC: C11.1, R39.1; also elsewhere on the board
/XY1_ADC: C6.1, U7.4; also elsewhere on the board
/Y0_ADC: C9.1, R38.1; also elsewhere on the board
GND: C16.2; also elsewhere on the board
GNDA: C6.2, C7.2, C8.2, C9.2, C10.2, C11.2, C17.2, C18.2, C19.2, C21.2, J26.3, J26.6, J27.3, J27.6, R28.1, R40.1, R41.1, R42.1, R43.1, TP7.1, U7.2 (GND), U9.2 (GND), U9.4 (NC); also elsewhere on the board
unnamed: C8.1, R37.1, U7.1
unnamed: C10.1, R36.1, U7.3
unnamed: J26.1, R37.2, R41.2
unnamed: J26.4, R36.2, R40.2
unnamed: J27.1, R39.2, R43.2
unnamed: J27.4, R38.2, R42.2
unnamed: C7.1, C17.1, L2.2, U9.1 (IN), U9.3 (EN)

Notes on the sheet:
3V3A
GND
Same connector as Radio Master TX16S

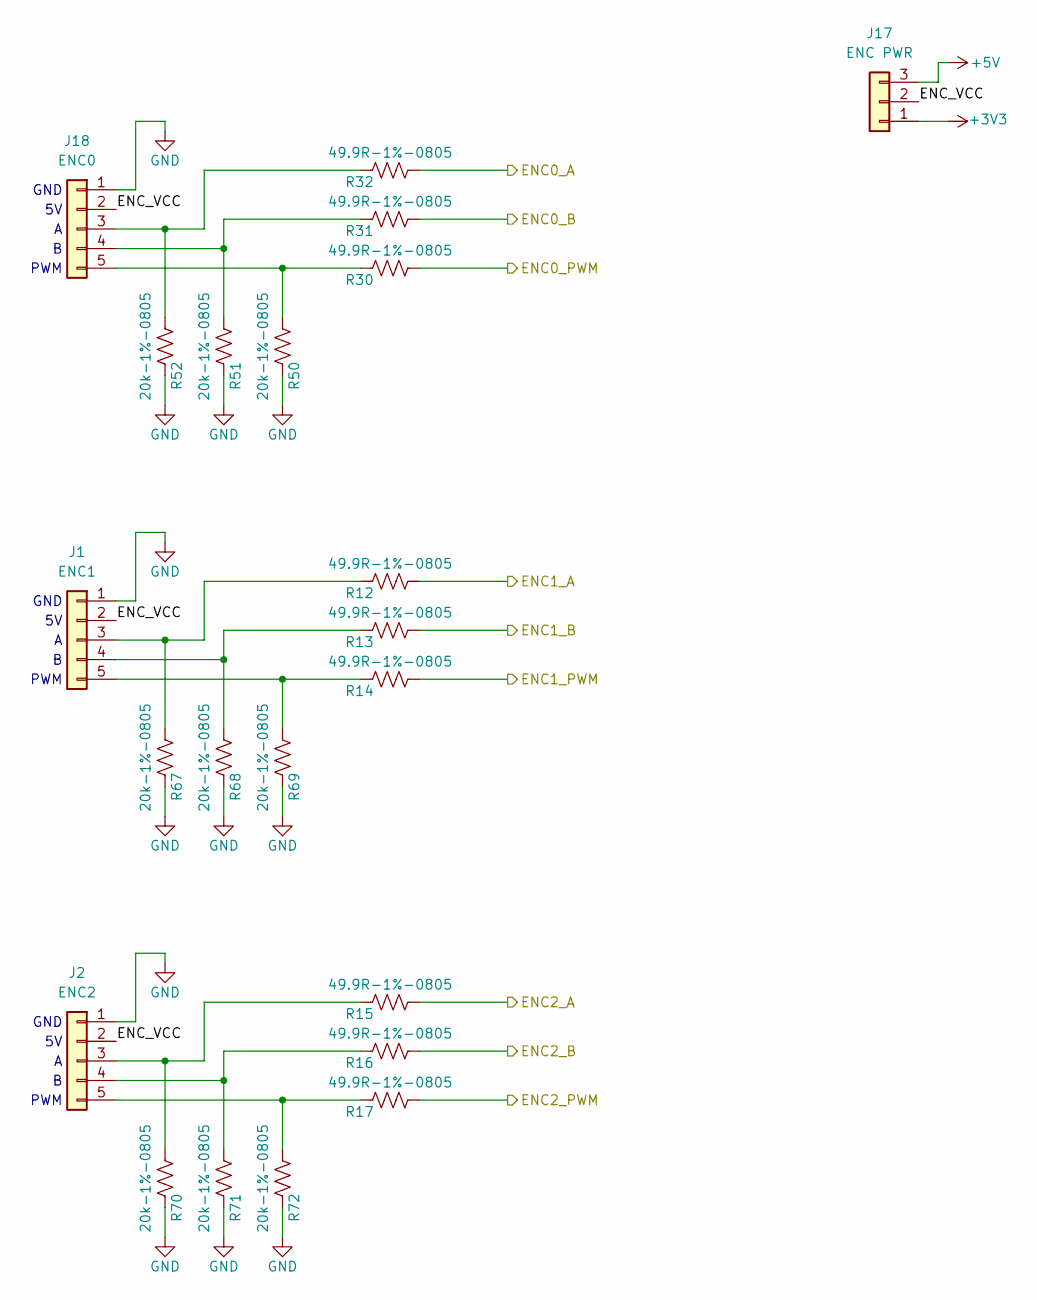
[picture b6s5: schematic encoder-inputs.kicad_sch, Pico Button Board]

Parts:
J1: ENC1; Molex-70543-0039; MFG P/N 0705430039
J2: ENC2; Molex-70543-0039; MFG P/N 0705430039
J17: ENC PWR; PinHeader_1x03_P2.54mm_Vertical
J18: ENC0; Molex-70543-0039; MFG P/N 0705430039
R12, R13, R14, R15, R16, R17, R30, R31, R32: 49.9R-1%-0805; R_0805_2012Metric_Pad1.20x1.40mm_HandSolder; MFG P/N RMCF0805FT49R9
R50, R51, R52, R67, R68, R69, R70, R71, R72: 20k-1%-0805; R_0805_2012Metric_Pad1.20x1.40mm_HandSolder; MFG P/N ERJ-6ENF2002V

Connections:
+3V3: J17.1; also elsewhere on the board
+5V: J17.3; also elsewhere on the board
/ENC0_A: R32.1; also elsewhere on the board
/ENC0_B: R31.1; also elsewhere on the board
/ENC0_PWM: R30.1; also elsewhere on the board
/ENC1_A: R12.1; also elsewhere on the board
/ENC1_B: R13.1; also elsewhere on the board
/ENC1_PWM: R14.1; also elsewhere on the board
/ENC2_A: R15.1; also elsewhere on the board
/ENC2_B: R16.1; also elsewhere on the board
/ENC2_PWM: R17.1; also elsewhere on the board
/Encoder Inputs/ENC_VCC: J1.2, J2.2, J17.2, J18.2
GND: J1.1, J2.1, J18.1, R50.1, R51.1, R52.1, R67.1, R68.1, R69.1, R70.1, R71.1, R72.1; also elsewhere on the board
unnamed: J1.3, R12.2, R67.2
unnamed: J1.4, R13.2, R68.2
unnamed: J1.5, R14.2, R69.2
unnamed: J2.3, R15.2, R70.2
unnamed: J2.4, R16.2, R71.2
unnamed: J2.5, R17.2, R72.2
unnamed: J18.3, R32.2, R52.2
unnamed: J18.4, R31.2, R51.2
unnamed: J18.5, R30.2, R50.2

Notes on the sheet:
GND
PWM
